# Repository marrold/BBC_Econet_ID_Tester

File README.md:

# Econet ID Tester

A project to use an Arduino Uno as a BBC Econet Station ID Tester. The intention is to use it when constructing [these modules](https://github.com/marrold/BBC_EcoID)

**Note:** It's currently untested

## License

- This project is licensed under the MIT license

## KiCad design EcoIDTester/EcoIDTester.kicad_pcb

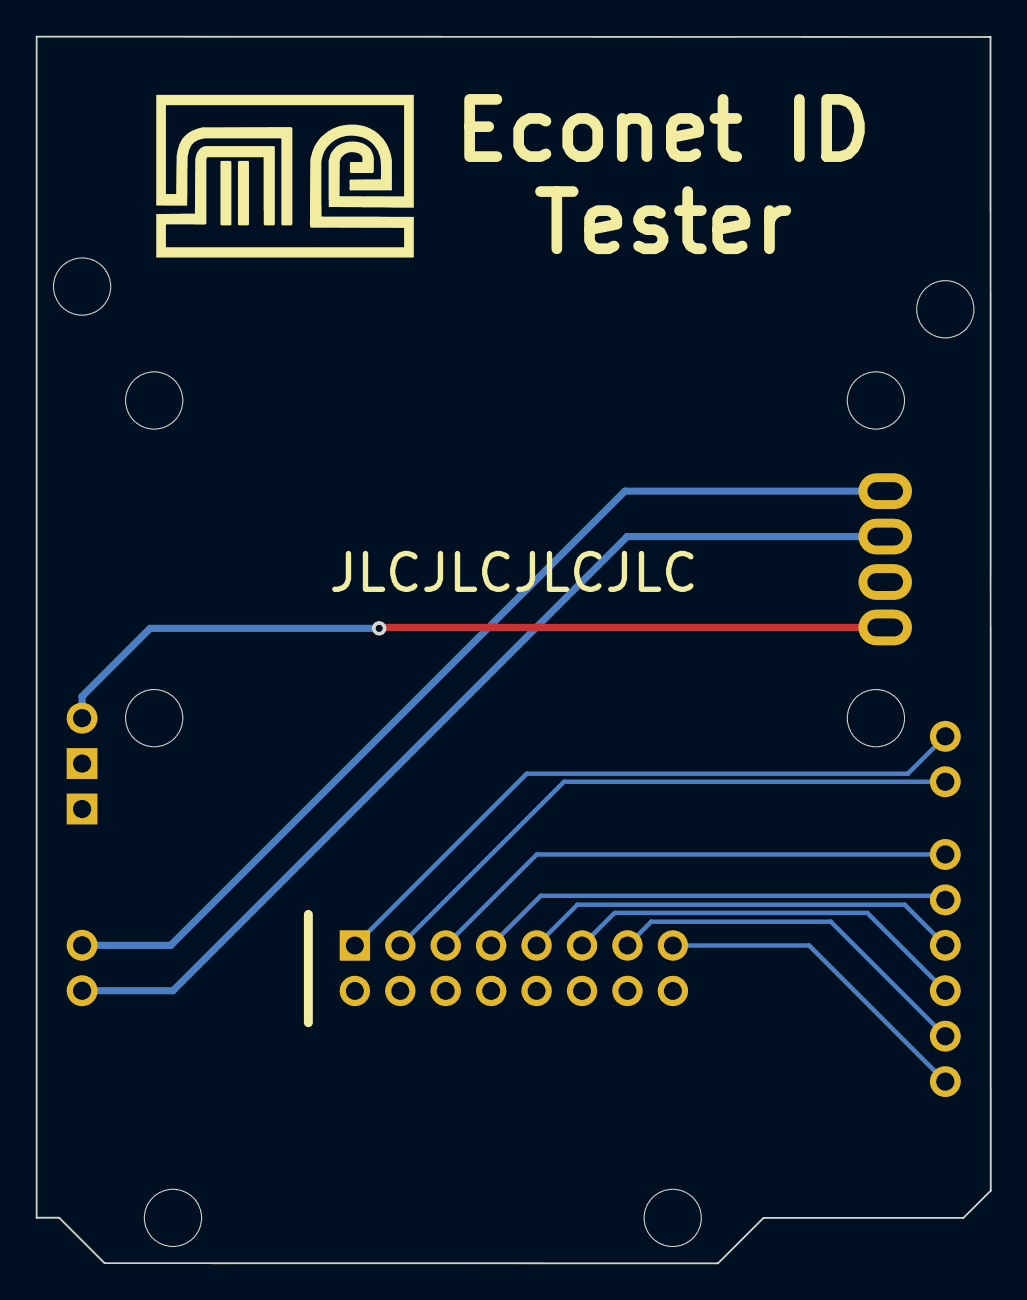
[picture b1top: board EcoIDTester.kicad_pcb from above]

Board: 2 copper layers, 53.3 x 68.6 mm, 3 parts (0 on the bottom side), 12 nets.

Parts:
A1: Arduino_Uno_R3_Shield
J1: Conn_02x08_Odd_Even; PinSocket_2x08_P2.54mm_Vertical
J2: Conn_01x04_Female; TM1637_Module

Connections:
+5V: A1.5V1 (5V), J2.4
/CLK: A1.A0, J2.1
/D2: A1.D2 (D2_INT0), J1.15
/D3: A1.D3 (D3_INT1), J1.13
/D4: A1.D4, J1.11
/D5: A1.D5, J1.9
/D6: A1.D6, J1.7
/D7: A1.D7, J1.5
/D8: A1.D8, J1.3
/D9: A1.D9, J1.1
/DIO: A1.A1, J2.2
GND: A1.GND2 (GND), A1.GND3 (GND), J1.2, J1.4, J1.6, J1.8, J1.10, J1.12, J1.14, J1.16, J2.3

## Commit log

2024-01-05 init
2024-01-05 Add README
2024-01-14 Add arduino code
2024-01-14 The Arduino IDE insists the dir name matches the .ino
